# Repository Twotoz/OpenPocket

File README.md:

<p align="center">

</p>

<p align="center">
  <strong>A compact all-in-one ESP32-S3 handheld PCB combining RivetTX, ExpressLRS, RX5808 video, AT7456E OSD, and an AMT630A-driven 5-inch TFT.</strong>
</p>

<p align="center"><em>Revision-A top and bottom placement previews — production-board text and signal routing intentionally omitted.</em></p>

<p align="center">
  <a href="#why-openpocket">Why OpenPocket</a> ·
  <a href="#architecture">Architecture</a> ·
  <a href="#hardware">Hardware</a> ·
  <a href="#build-path">Build path</a> ·
  <a href="#firmware">Firmware</a> ·
  <a href="#documentation">Documentation</a>
</p>

> [!CAUTION]
> OpenPocket is an engineering prototype, not a flight-proven product. Build
> the first revision on a current-limited bench supply. Keep propellers removed
> and mechanisms safe until your exact transmitter, failsafe, power system,
> RF link, and video chain have passed hardware-in-the-loop validation.

## Why OpenPocket

OpenPocket puts the controls, live analog FPV picture, and transmitter menus in
one compact handheld. It uses the existing RivetTX OpenPocket character
compositor unchanged and connects it to a physical AT7456E video-overlay
backend. The ESP32 never has to capture or process video pixels.

| | |
|---|---|
| **One handheld** | Gimbals, switches, ExpressLRS control, telemetry, video, and menus in a single enclosure. |
| **Purpose-built MCU** | ESP32-S3 provides the GPIO, native USB, and task separation needed by the complete controller. |
| **Low-latency video** | RX5808 composite video passes through the AT7456E into an AMT630A TFT controller without digital capture. |
| **Integrated snow-screen display** | The PCB-installed AMT630A keeps weak or lost analog video visible as noise instead of hiding it behind a blue screen. |
| **Native analog OSD** | PAL/NTSC autodetection, a 30×16 character grid, custom glyphs, delta updates, and video-loss recovery. |
| **Bounded background work** | OSD and receiver services cannot delay control, CRSF, or telemetry processing. |
| **Open development path** | Wiring, BOM decisions, bring-up evidence, and future KiCad sources live in this repository. |

## Architecture

The flight-control path stays short while video and presentation work run as
bounded services.

```mermaid
flowchart LR
    A[Gimbals + switches] --> B[ESP32-S3<br/>RivetTX]
    B --> C[CRSF UART]
    C --> D[ExpressLRS<br/>TX module]

    E[5.8 GHz antenna] --> F[RX5808]
    F -->|composite video| G[AT7456E]
    G -->|internal PCB trace| H[AMT630A<br/>on the same PCB]
    H -->|24-bit RGB + sync| I[AT050TN33 V.1<br/>40-pin TFT]

    B -->|tune + RSSI| F
    B -->|bounded SPI| G
    D -->|telemetry| B

    classDef control fill:#102a43,stroke:#38bdf8,color:#f8fafc;
    classDef video fill:#26163f,stroke:#a78bfa,color:#f5f3ff;
    class A,B,C,D control;
    class E,F,G,H,I video;
```

The 250 Hz control task owns channel output and safety. The OSD driver advances
a non-blocking state machine and writes only changed character runs. Video
loss, PAL/NTSC changes, or an absent OSD chip must never hold up the control
path.

## Hardware

| Component | Role |
|---|---|
| ESP32-S3-MINI-1U-N8 | PCB-installed RivetTX MCU, native USB, 8 MiB flash, no PSRAM |
| user-installed ExpressLRS nano receiver | four-wire full-duplex CRSF control and telemetry link |
| PCBWay-installed RX5808 module | tunable 5.8 GHz analog receiver, internal composite video, and RSSI |
| PCB-installed AT7456E | PAL/NTSC character overlay in the internal video path |
| PCB-installed AMT630A and flash | PAL/NTSC composite decoding and direct 24-bit RGB panel drive |
| AT050TN33 V.1-compatible TFT | user-plugged 40-pin panel; arbitrary 40-pin TFTs are unsupported |
| two dual-axis gimbals | four primary analog control axes |
| switches, menu buttons, and optional encoder | arming, AUX controls, navigation, and editing |
| validated regulators and protection | clean supplies sized for RF, display, video, and logic peaks |

The ESP32-S3 is the OpenPocket target. RivetTX may support smaller ESP32-C3
transmitters, but the C3 is not the reference platform for this handheld. See
[ADR-0001](docs/decisions/0001-esp32-s3.md) for the decision record.

## Analog OSD

The existing RivetTX compositor produces a hardware-independent 30-column by
16-row character frame. The AT7456E backend then provides:

- PAL/NTSC autodetection and safe standard changes without a reboot
- all 30×16 cells in PAL, with essential content held inside 30×13 for NTSC
- custom character uploads for icons, selection markers, and warnings
- shadow-frame comparison so unchanged cells generate no SPI traffic
- bounded asynchronous transfers instead of full-screen blocking redraws
- communication retry/backoff and redraw after video loss or recovery

The RX5808 feeds baseband video to the AT7456E over an internal PCB trace; the
AT7456E overlays text and passes it internally to the AMT630A, which drives the
edge-connected TFT directly. The user never wires composite video. The
AMT630A's internal OSD is not used for OpenPocket menus. See the
[complete wiring guide](docs/wiring.md).

## Build path

Bring up one subsystem at a time:

1. Review the [Revision-A engineering package](hardware/rev-a/README.md) and
   resolve every machine-readable release blocker.
2. Complete independent schematic, layout, sourcing, and Gerber reviews.
3. Assemble first articles through PCBWay with the RX5808 consigned/manual
   operation and no unapproved substitutions.
4. Power the board from a current-limited source and validate rails before
   inserting the TFT, battery, or ExpressLRS receiver.
5. Complete the factory and HIL gates before any propeller-on use.

The [bench build guide](docs/build-guide.md) contains the full sequence and
stop conditions. Do not order from provisional files or bypass the release
gate in `hardware/rev-a`.

## Firmware

OpenPocket runs the `main` branch of
[Twotoz/RivetTX](https://github.com/Twotoz/RivetTX):

```bash
git clone https://github.com/Twotoz/RivetTX.git
cd RivetTX
idf.py set-target esp32s3
idf.py menuconfig
idf.py build
idf.py flash monitor
```

Use RivetTX's checked-in `sdkconfig.openpocket-rev-a.defaults`; it contains the
authoritative no-PSRAM, 8 MiB flash configuration and GPIO map matching this
board. See the [firmware guide](docs/firmware.md) for the complete configuration.

## Documentation

| Document | Contents |
|---|---|
| [Bill of materials](docs/bom.md) | prototype parts, electrical requirements, and unresolved selections |
| [Wiring](docs/wiring.md) | ESP32-S3, RX5808, AT7456E, AMT630A, TFT, and ExpressLRS interconnects |
| [Bench build guide](docs/build-guide.md) | staged assembly sequence and stop conditions |
| [Firmware](docs/firmware.md) | ESP32-S3 target setup and RivetTX OSD configuration |
| [Bring-up checklist](docs/bring-up.md) | electrical, control, PAL/NTSC, failure-recovery, and endurance tests |
| [Architecture](docs/architecture.md) | task boundaries, character presentation, and video path |
| [ESP32-S3 decision](docs/decisions/0001-esp32-s3.md) | why OpenPocket standardizes on the S3 |
| [AMT630A display decision](docs/decisions/0002-amt630a-snow-screen.md) | why the display stage uses a snow-screen AMT630A board |
| [Hardware sources](hardware/README.md) | scope and release policy for future KiCad and production files |
| [Revision-A package](hardware/rev-a/README.md) | integrated board constraints, GPIO, power, BOM, factory test, and release gates |
| [AMT630A firmware](display/amt630a/README.md) | target behavior, provenance requirements, and deterministic build gate |

## Project status

RivetTX contains the character OSD and physical RX5808/AT7456E services, with
host coverage for PAL, NTSC, UI, tuning, scanning, RSSI, delta updates, glyphs,
loss/recovery, and failure isolation. Revision-A startup ordering, board power
policy, and the no-PSRAM pin/partition profile are under review.

No PCB order package is released yet. The exact panel datasheet, AMT630A
firmware rights/provenance, selected RX5808 consigned module, sourcing review,
KiCad ERC/DRC, Gerber inspection, and physical HIL evidence remain open. This
is intentionally an engineering prototype, not a production-ready product.

## Contributing

Issues, schematic reviews, module measurements, and focused pull requests are
welcome. Hardware findings must identify the exact module revision, voltage,
firmware commit, measurement point, and PAL/NTSC source. See
[CONTRIBUTING.md](CONTRIBUTING.md).

## License

OpenPocket documentation and future hardware sources are released under the
[MIT License](LICENSE). RivetTX is maintained in its own repository under its
own license.

---

<p align="center">
  <sub>Built for open hardware experimentation, low-latency analog FPV, and careful validation.</sub>
</p>

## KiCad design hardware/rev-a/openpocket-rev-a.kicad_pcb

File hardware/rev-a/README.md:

# OpenPocket Revision A — Engineering Prototype

Revision A is a 115 mm × 72 mm, eight-layer, all-in-one transmitter board based
on the ESP32-S3-MINI-1U-N8. The intended assembled signal path is:

```text
5.8 GHz antenna -> RX5808 -> AT7456E -> AMT630A -> 40-pin ER-TFT050A3-2
```

Composite video never leaves the PCB. JLCPCB Standard PCBA is the primary
assembly target, with pre-order and consigned-RX5808 variants; the design is
vendor-neutral. The user installs
only the TFT panel, controls, one wired protected 1S battery connection,
antennas, a pre-flashed ExpressLRS nano receiver, and the enclosure.

## Release state

This directory is an engineering-review package, not an order package. The
release script intentionally refuses to generate Gerbers or a manufacturing
ZIP until every blocking item in `release-status.json` is resolved with a
reviewed source artifact.

The generated KiCad draft has a clean ERC and a completed L2 ground fanout,
but signal routing and final DRC remain incomplete. It is therefore not a
fabrication/order package. The source-built AMT630A firmware and circuit
research may be reviewed independently, but they do not waive schematic,
layout, Gerber and first-article gates. Software tests are not hardware
validation.

## Design constraints

- 115 mm × 72 mm fixed outline.
- Eight layers, 1.0 mm finished thickness, 1 oz copper, ENIG.
- L1/L8 components and critical routing, uninterrupted L2/L7 ground, and six
  available routing layers for signals and width-controlled power routes.
- RX5808 on the bottom side with shield, solder-joint, antenna and inspection
  clearances; J11 U.FL/MHF1 is also bottom-side for a via-free 5.8 GHz feed.
- AMT630A next to the edge-mounted TFT connector; AT7456E on the short analog
  path between RX5808 and AMT630A.
- Backlight switching and power converters stay outside the analog/RF region.
- Separate ESP32, ELRS 2.4 GHz, and RX5808 5.8 GHz antenna regions.
- Dedicated user-accessible push-push microSD at 1-bit/20 MHz maximum, with
  switched power and enclosure finger/eject clearance.
- Board marking: `OpenPocket Rev A` and `Engineering Prototype`.

## Contents

| File | Purpose |
|---|---|
| `gpio-map.md` | authoritative ESP32 and expander allocation |
| `microsd.md` | SDMMC circuit, socket audit, limits and acceptance tests |
| `wiring.md` | internal and user-installed connections |
| `power-budget.md` | preliminary worst-case and thermal calculations |
| `routing-constraints.md` | KiCad netclasses, widths, vias and routing order |
| `stackup.md` | nominal 1.0 mm eight-layer construction and impedance sign-off gate |
| `bom.csv` | controlled component selection and verification state |
| `dnp.csv` | optional/DNP items |
| `consigned-parts.csv` | RX5808 manual-assembly requirement |
| `release-status.json` | machine-readable evidence and blockers |
| `factory-test.md` | pass/fail protocol and first-article sequence |
| `pcbway-notes.md` | stack-up, assembly, inspection, and substitution rules |
| `tools/release_gate.py` | refuses an unsafe manufacturing release |

Fabrication outputs and a versioned release ZIP must only be generated after
the KiCad sources pass review, ERC, DRC and independent Gerber inspection.

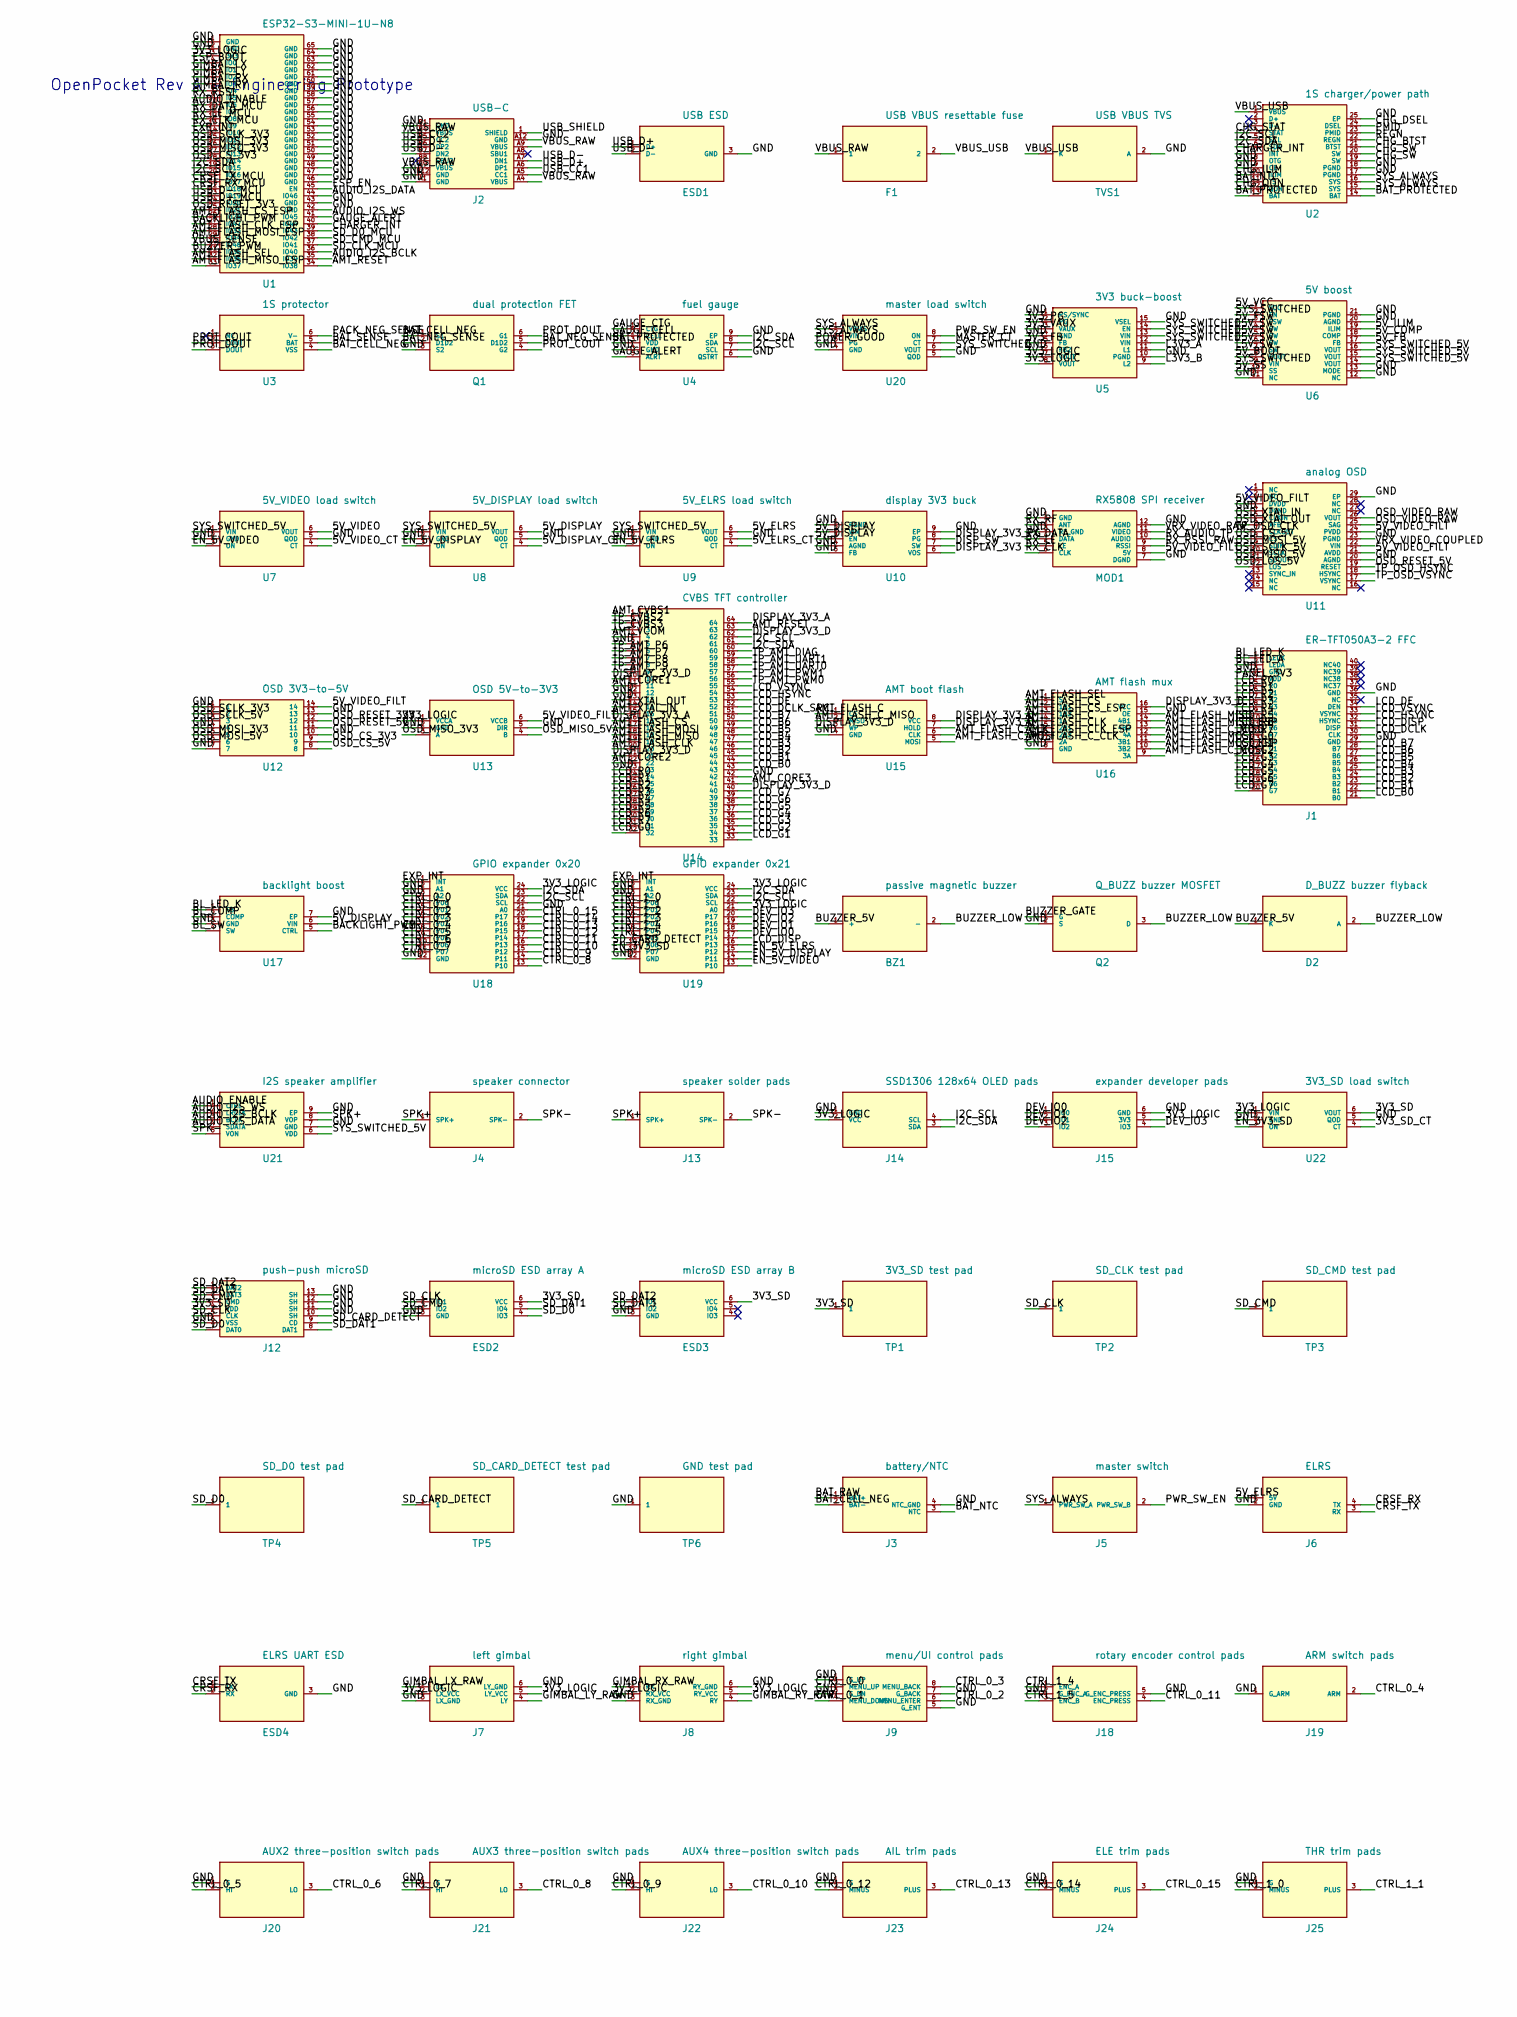
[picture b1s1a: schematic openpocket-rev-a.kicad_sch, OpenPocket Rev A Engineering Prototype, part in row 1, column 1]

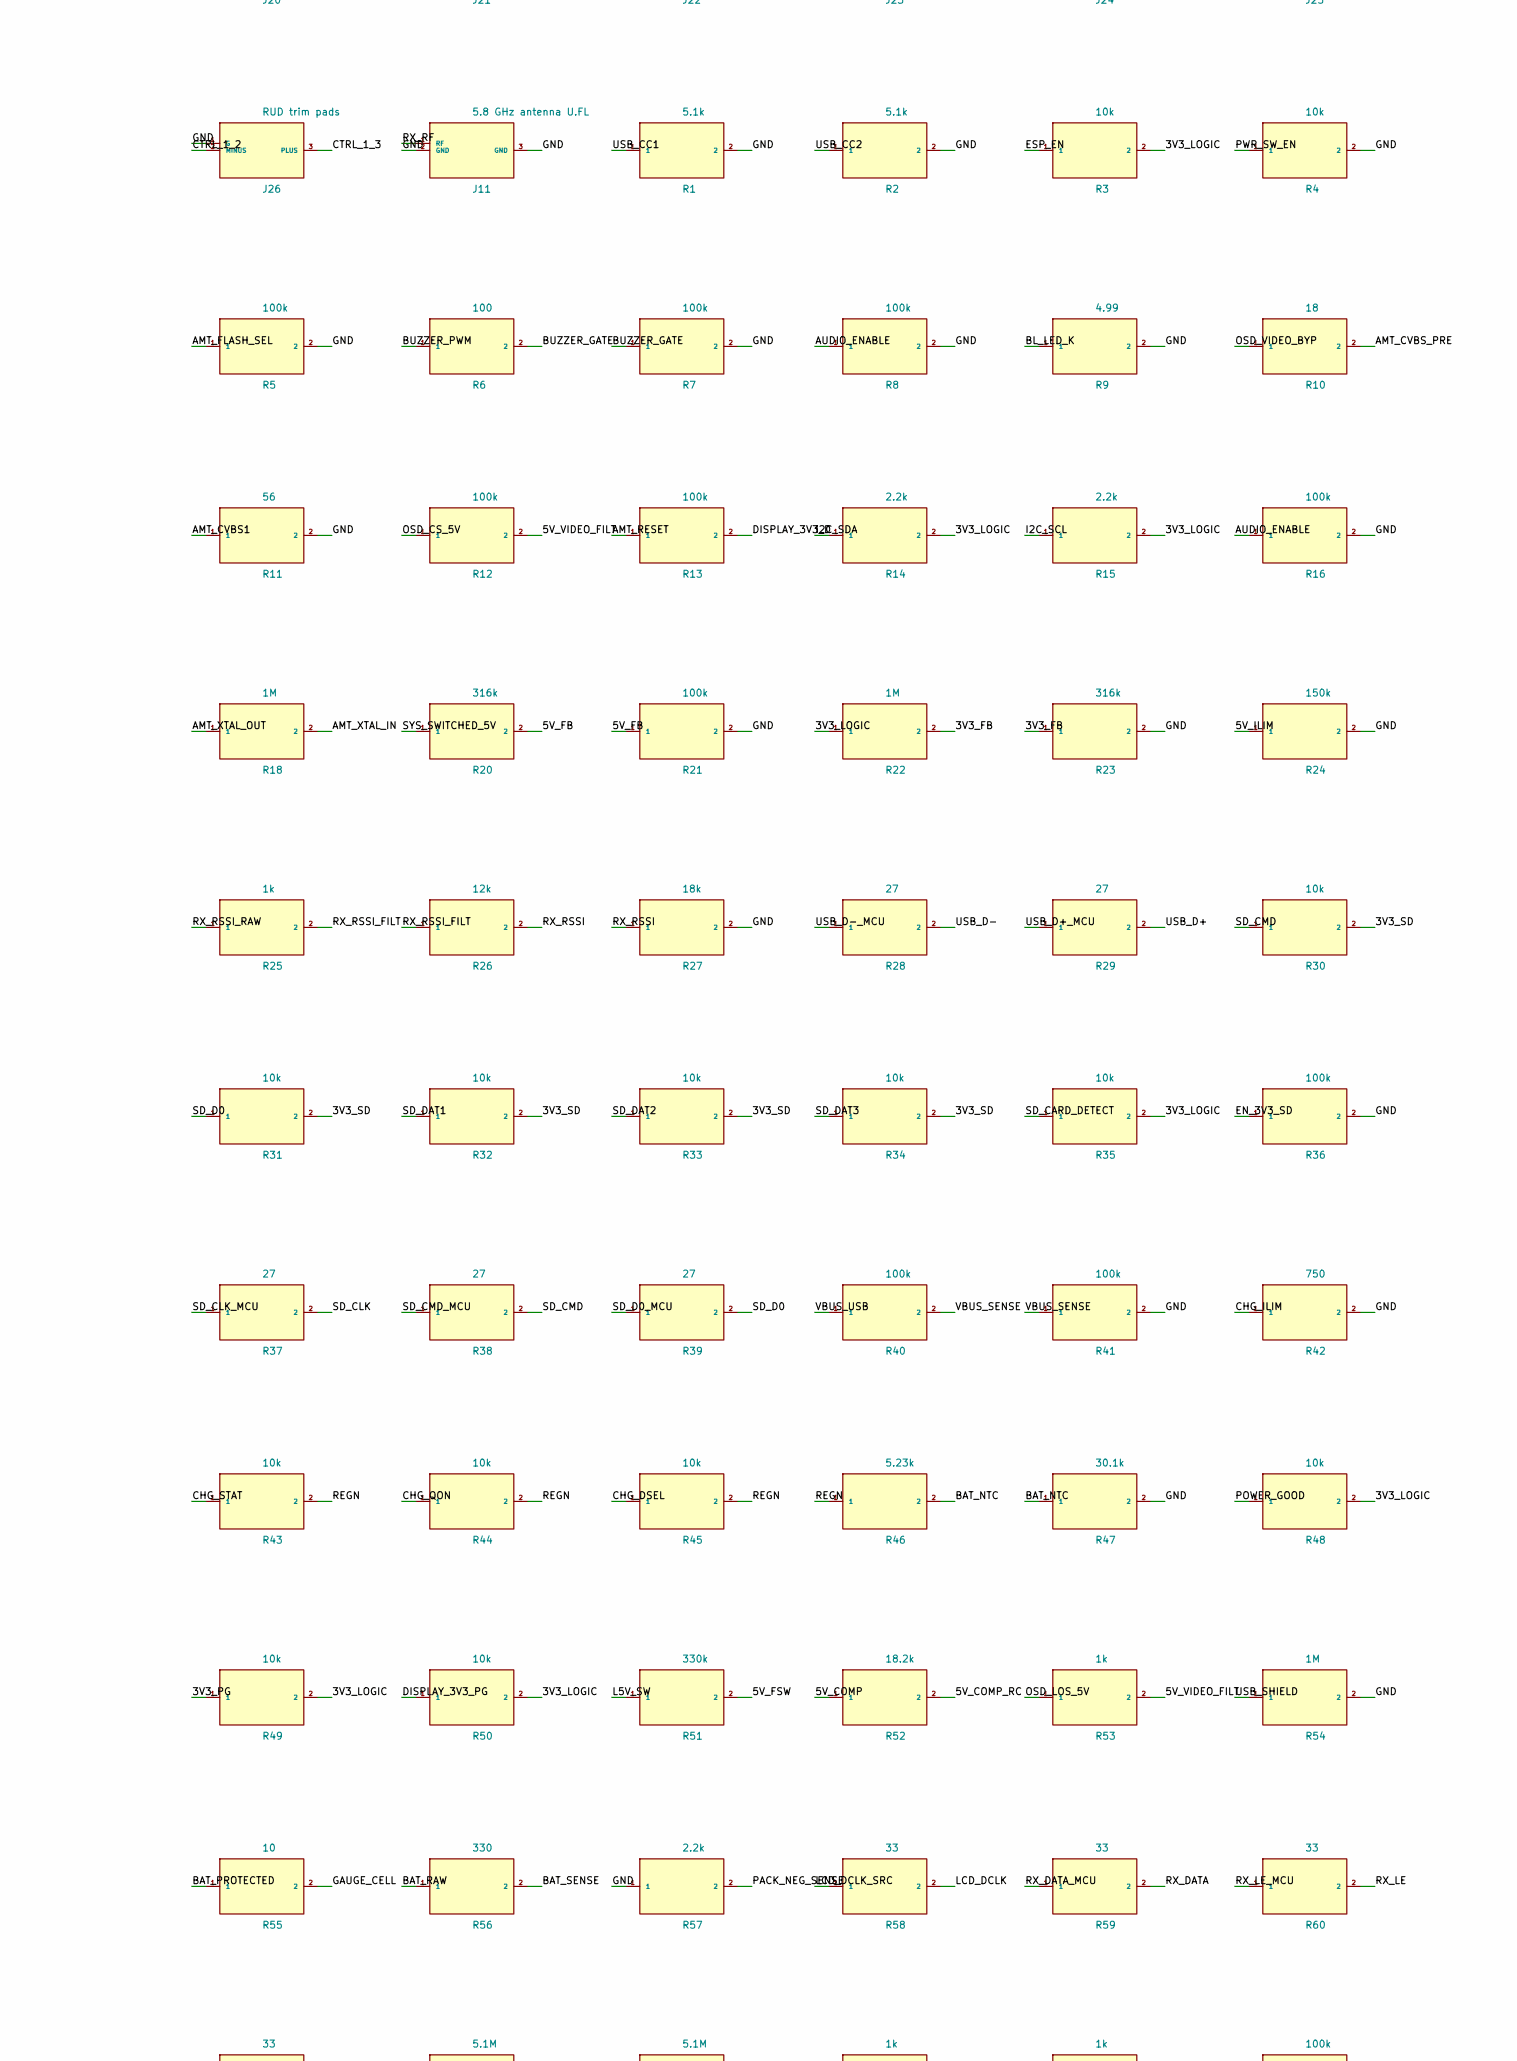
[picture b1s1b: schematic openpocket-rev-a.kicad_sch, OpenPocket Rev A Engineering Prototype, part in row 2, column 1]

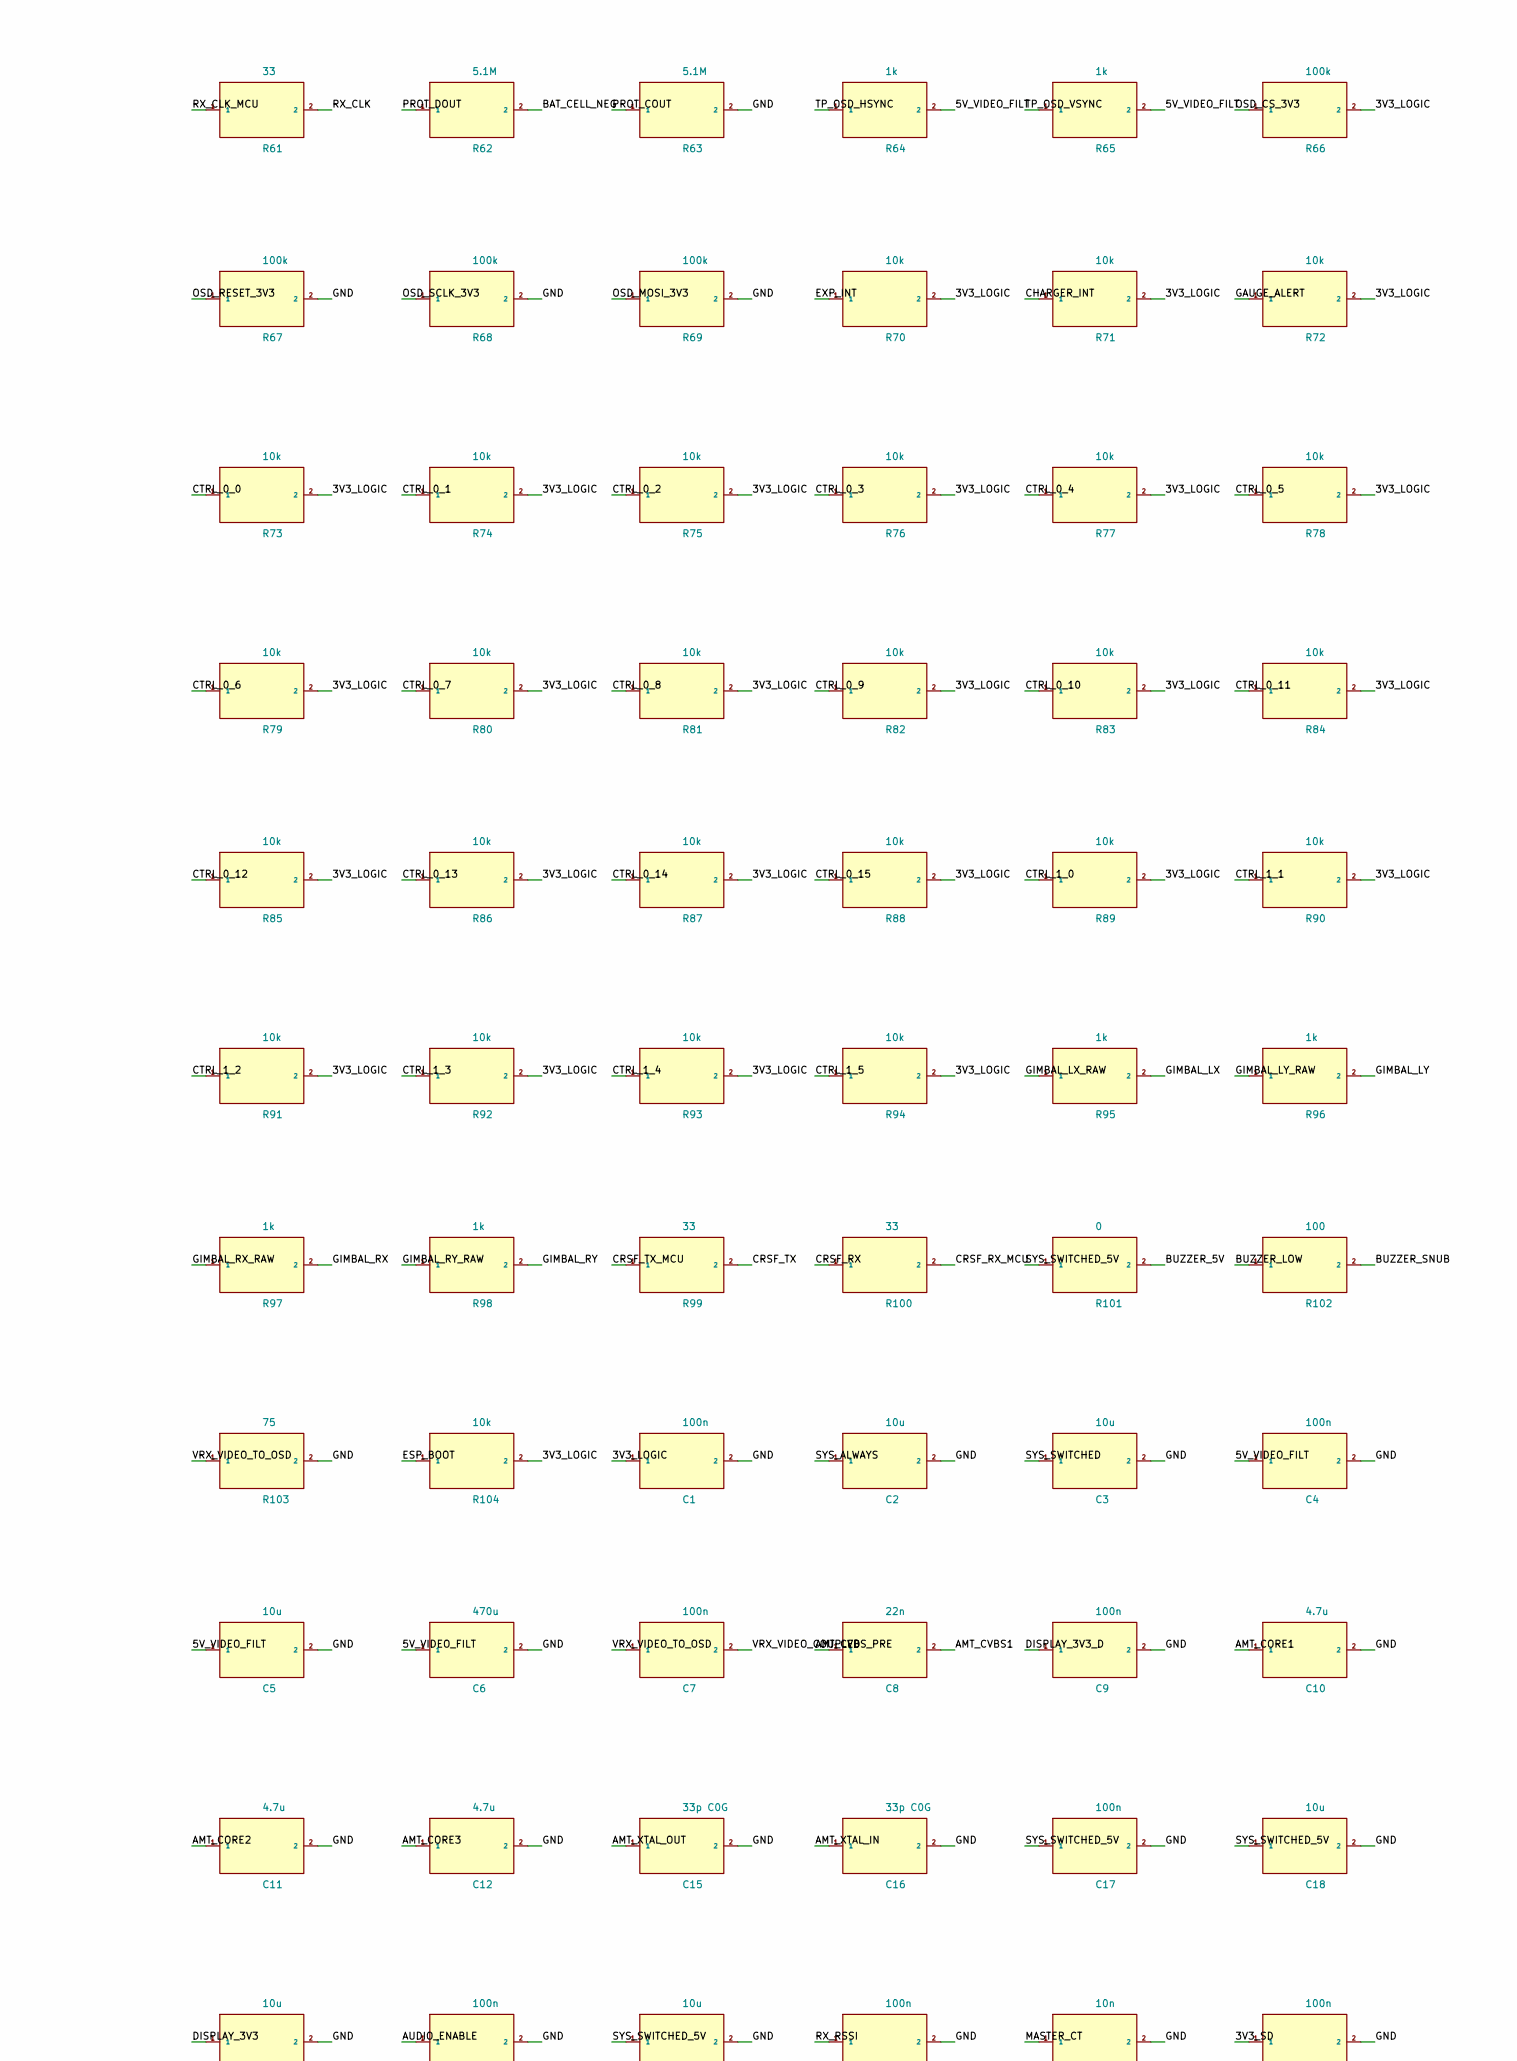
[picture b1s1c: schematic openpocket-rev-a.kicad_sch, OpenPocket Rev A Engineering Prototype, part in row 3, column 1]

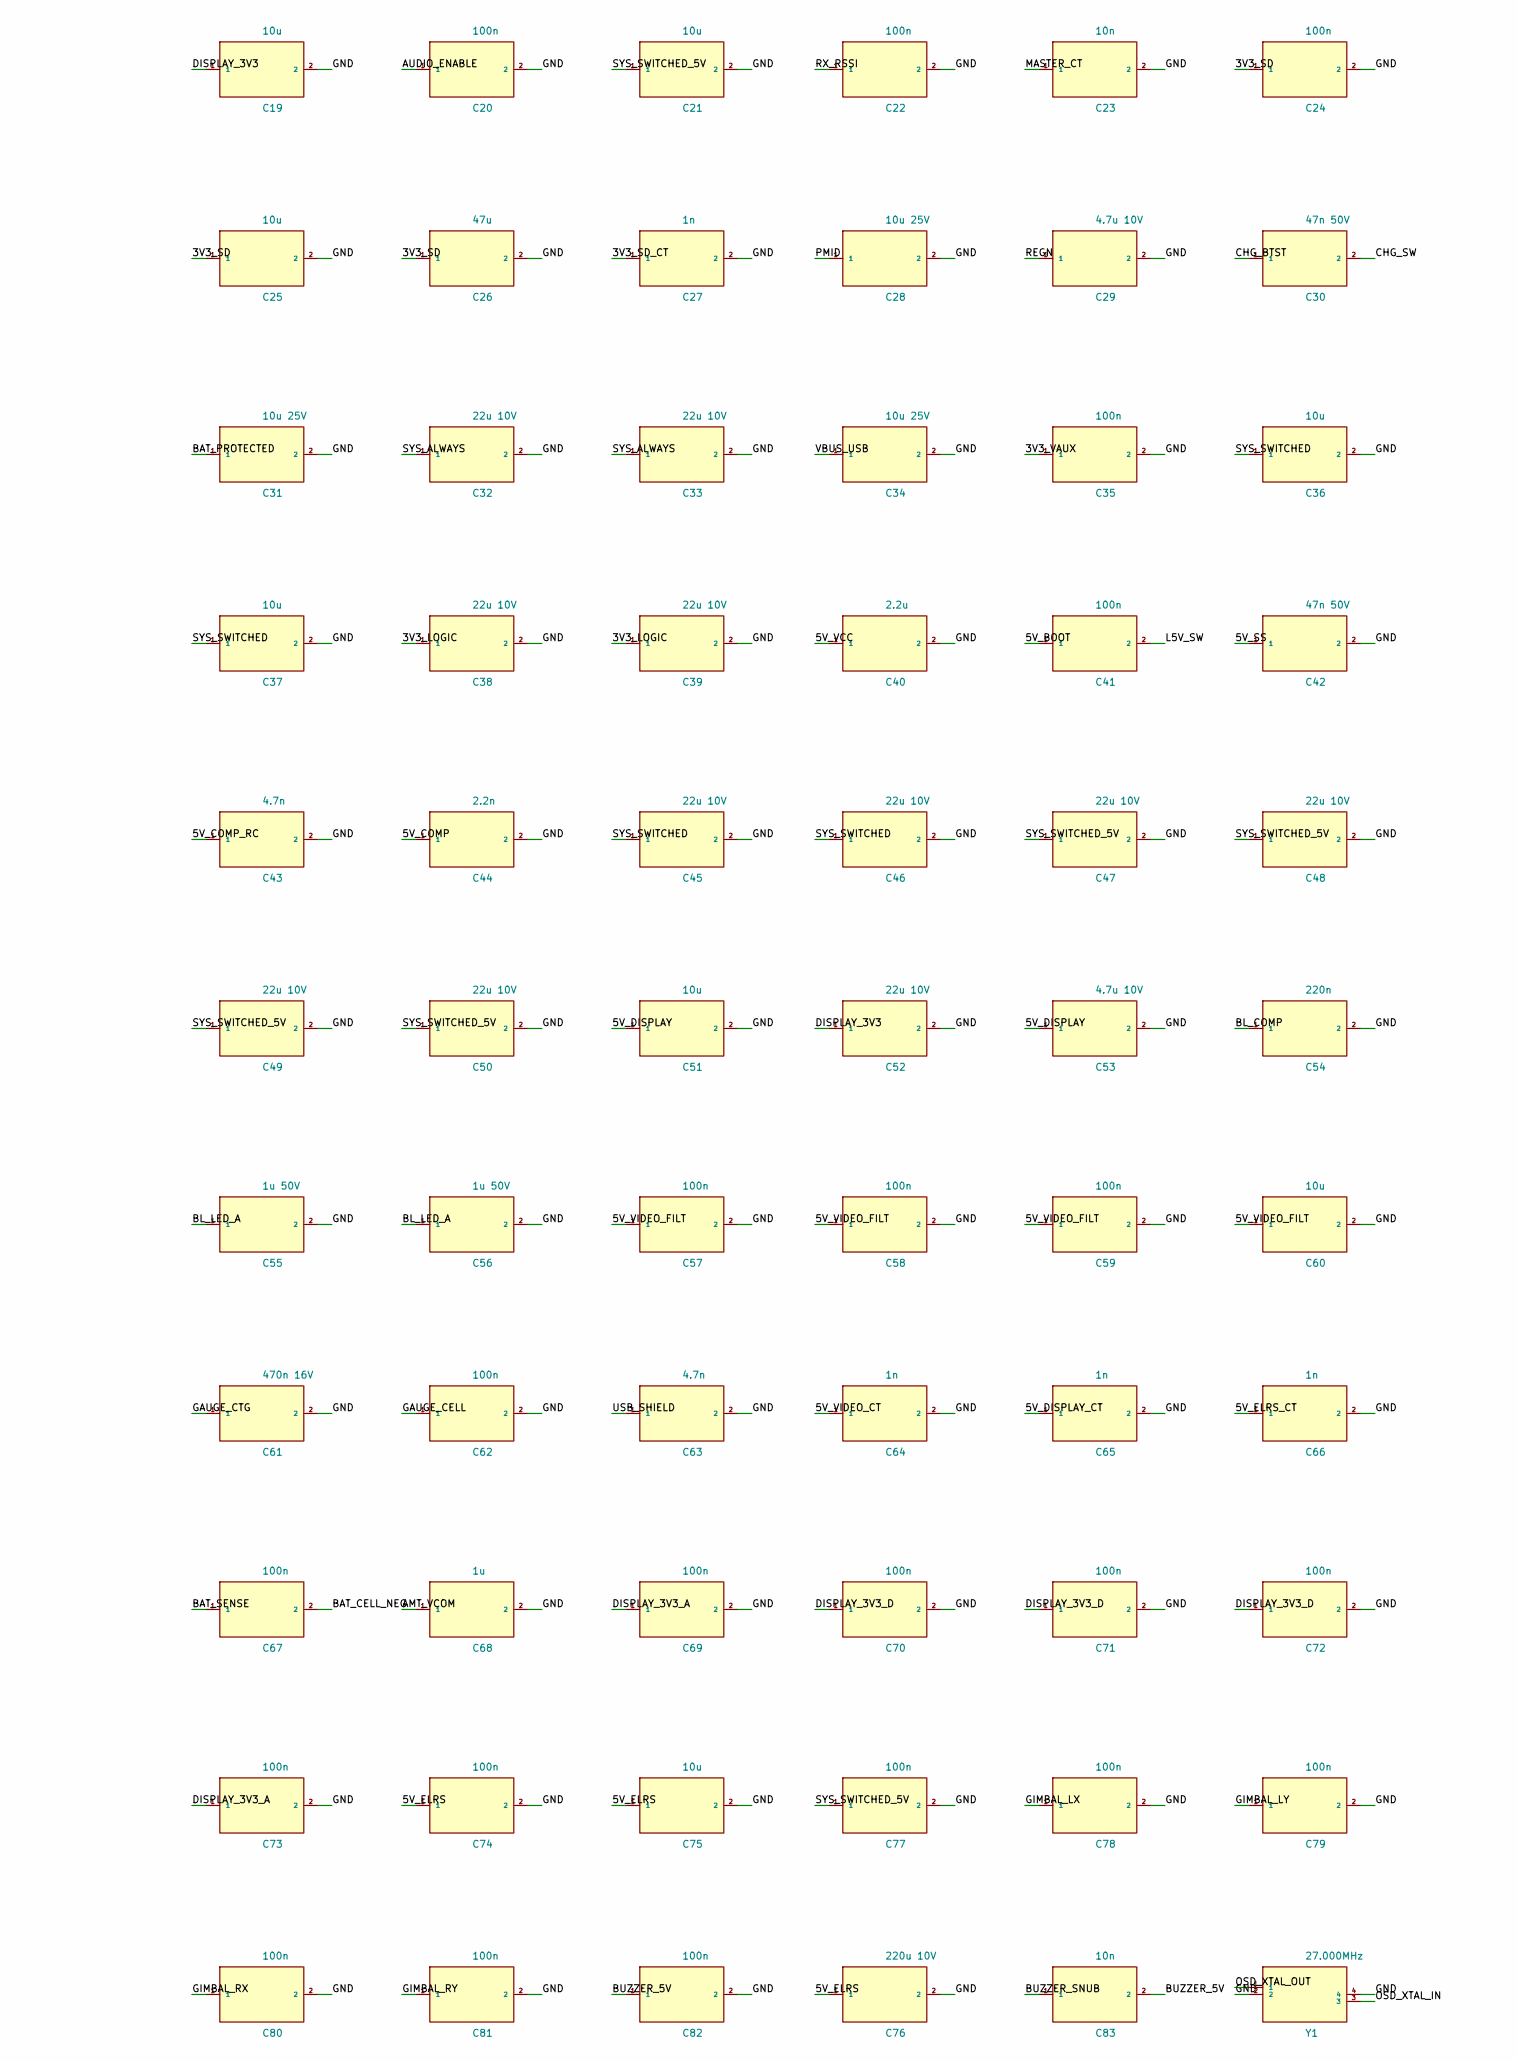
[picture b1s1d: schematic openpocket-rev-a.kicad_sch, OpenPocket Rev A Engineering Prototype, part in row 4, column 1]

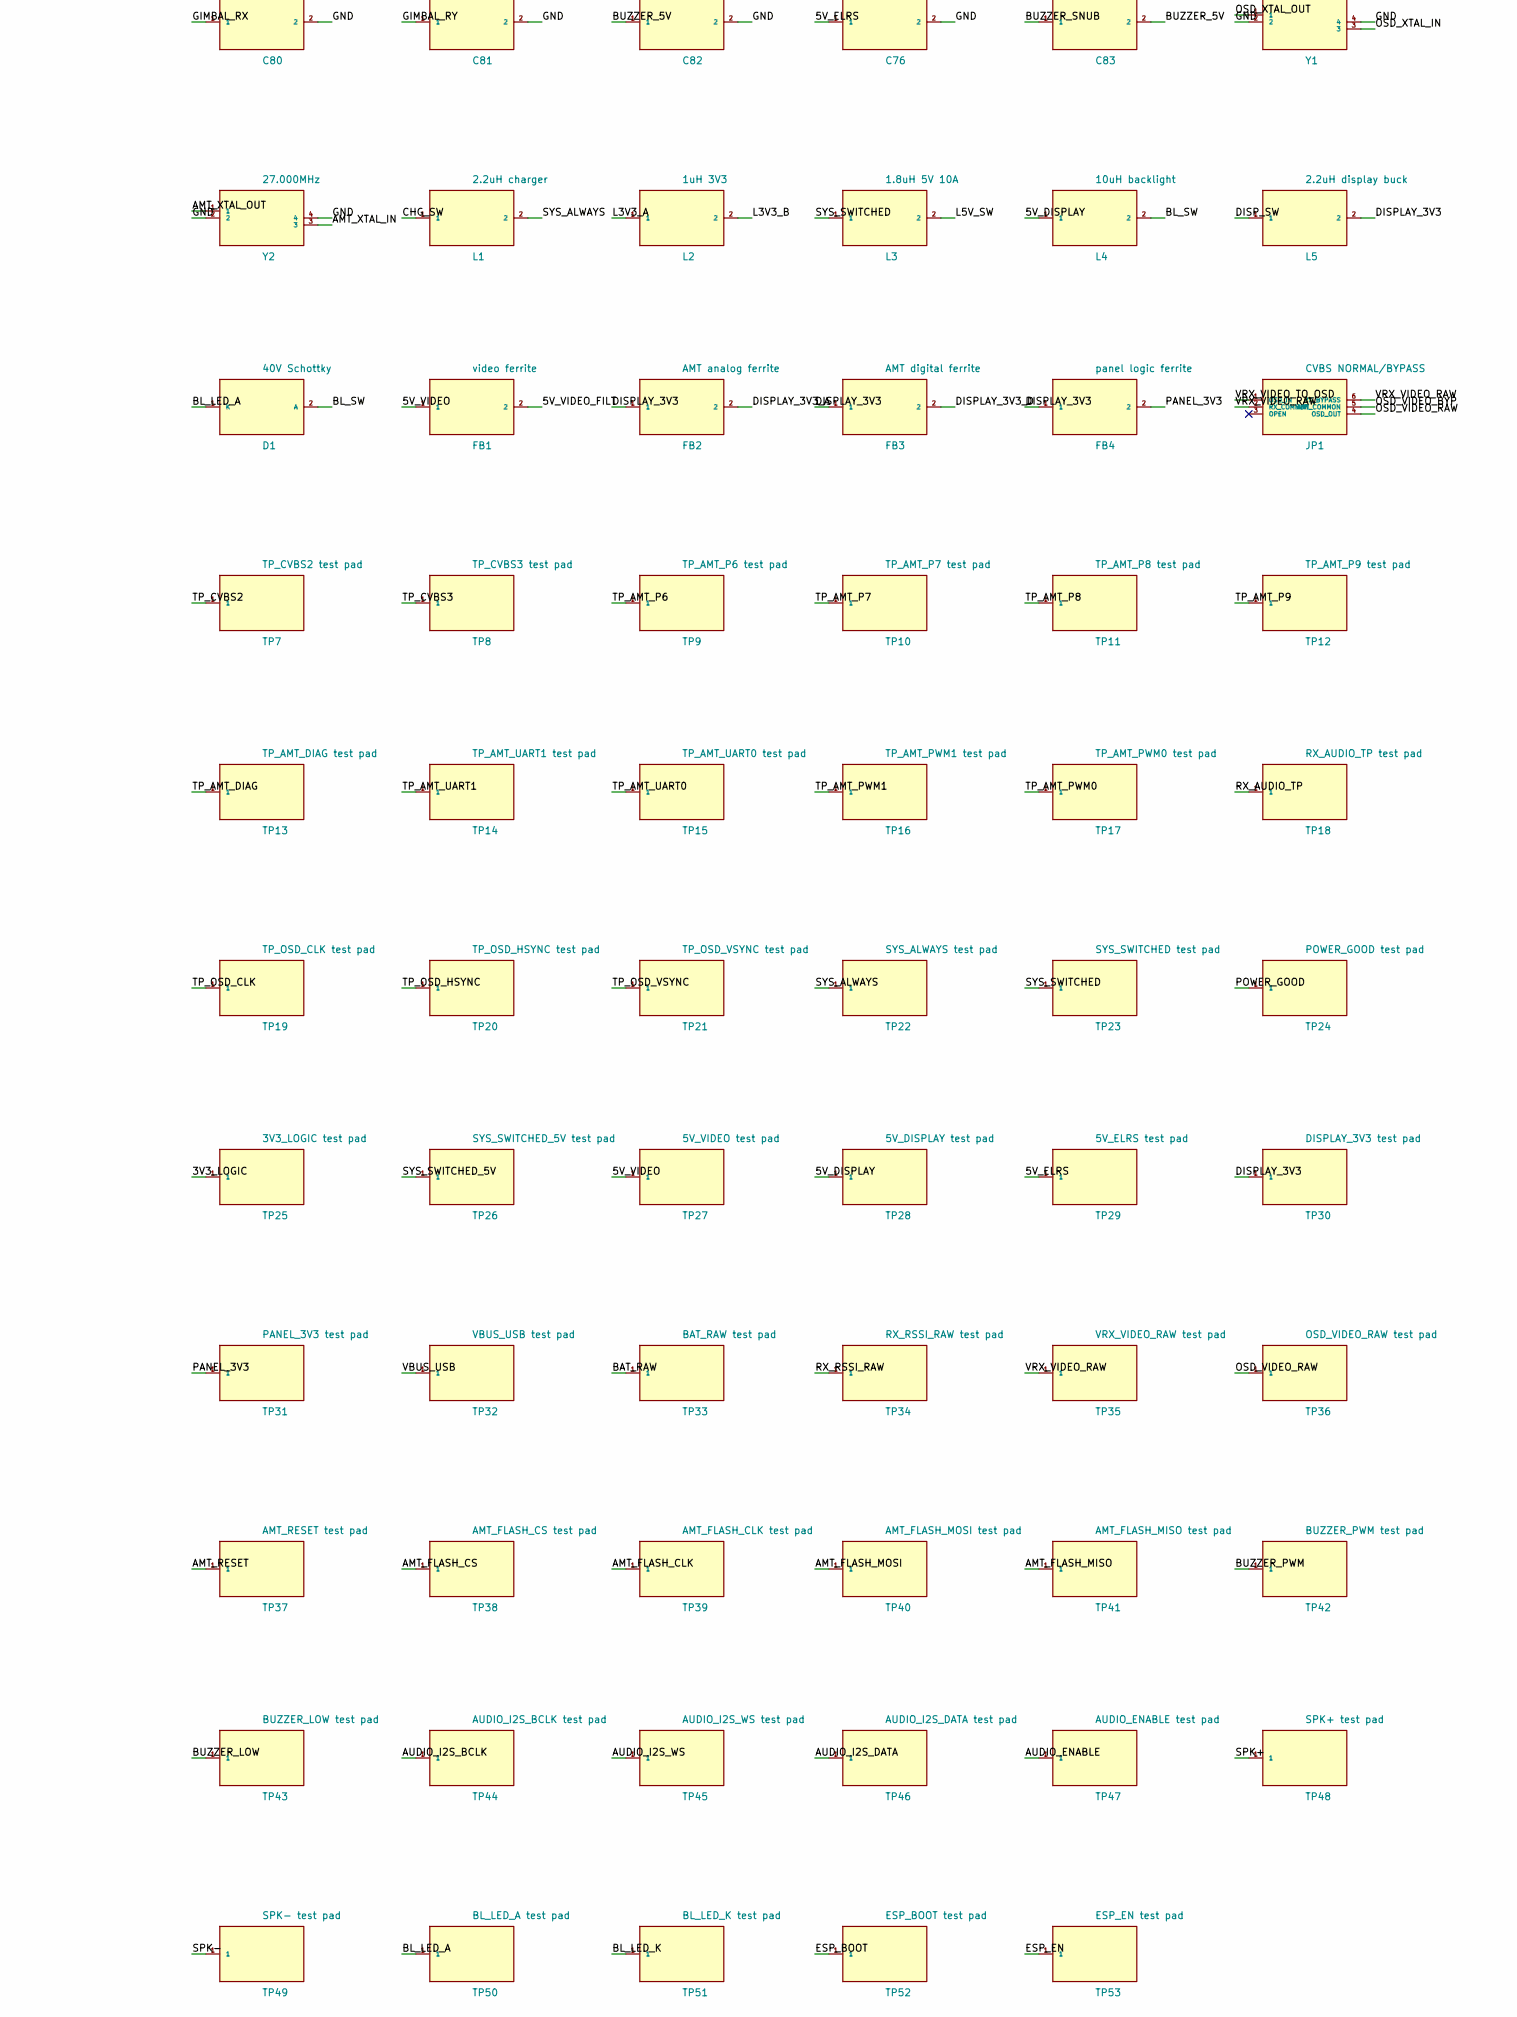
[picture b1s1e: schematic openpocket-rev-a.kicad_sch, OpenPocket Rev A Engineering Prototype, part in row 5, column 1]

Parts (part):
BZ1: passive magnetic buzzer; SMD-7.5x7.5; MPN YS-SBZ7525C05R30; LCSC C7421675
C1, C4, C7, C9, C17, C20, C22, C24, C35, C41, C57, C58, C59, C62, C67, C69, C70, C71, C72, C73, C74, C77, C78, C79, C80, C81, C82: 100n; C0402; MPN CL05B104KO5NNNC; LCSC C1525
C2, C3, C5, C18, C19, C21, C25, C36, C37, C51, C60, C75: 10u; C0805; MPN CL21A106KAYNNNE; LCSC C15850
C6: 470u; SMD-D10; MPN VZH471M1ATR-1008; LCSC C249929
C8: 22n; C0402; MPN CL05B223KB5NNNC; LCSC C337699
C10, C11, C12: 4.7u; C0603; MPN CL10A475KP8NNNC; LCSC C1705
C15, C16: 33p C0G; C0402; MPN CC0402JRNPO9BN330; LCSC C107005
C23, C83: 10n; C0402; MPN CL05B103KB5NNNC; LCSC C15195
C26: 47u; C1206; MPN CL31A476MPHNNNE; LCSC C96123
C27, C64, C65, C66: 1n; C0402; MPN CL05B102KB5NNNC; LCSC C14442
C28, C31, C34: 10u 25V; C0805; MPN CGA0805X7R106K250MT; LCSC C6119932
C29, C53: 4.7u 10V; 0603; MPN 0603B475K100NT; LCSC C108342
C30, C42: 47n 50V; C0402; MPN CC0402KRX7R9BB473; LCSC C272875
C32, C33, C38, C39, C45, C46, C47, C48, C49, C50, C52: 22u 10V; C0805; MPN CGA0805X7R226M100MT; LCSC C23692981
C40: 2.2u; C0603; MPN CL10A225KO8NNNC; LCSC C23630
C43, C63: 4.7n; C0402; MPN CL05B472KB5NNNC; LCSC C84705
C44: 2.2n; C0402; MPN CL05B222KB5NNNC; LCSC C84703
C54: 220n; C0402; MPN CC0402KRX7R8BB224; LCSC C723566
C55, C56: 1u 50V; C0805; MPN CC0805KKX7R9BB105; LCSC C91185
C61: 470n 16V; 0402; MPN CGA0402X7R474K160GT; LCSC C22435970
C68: 1u; C0402; MPN CL05A105KA5NQNC; LCSC C52923
C76: 220u 10V; CAP-SMD_BD8.0-L8.3-W8.3-FD; MPN EEEFK1A221P; LCSC C401648
D1: 40V Schottky; SMA_L4.3-W2.6-LS5.2-RD; MPN B240A-13-F; LCSC C92506
D2: D_BUZZ buzzer flyback; SOD-123F_L2.7-W1.6-LS3.8-RD; MPN 1N4148W; LCSC C81598
ESD1: USB ESD; SOT-9X3-3_L1.0-W0.8-P0.35-LS1.0-BR; MPN TPD2EUSB30DRTR; LCSC C97502
ESD2: microSD ESD array A; SOT-563_L1.6-W1.2-P0.50-LS1.6-BL; MPN TPD4E001DRLR; LCSC C527516
ESD3: microSD ESD array B; SOT-563_L1.6-W1.2-P0.50-LS1.6-BL; MPN TPD4E001DRLR; LCSC C527516
ESD4: ELRS UART ESD; SOT-9X3-3_L1.0-W0.8-P0.35-LS1.0-BR; MPN TPD2EUSB30DRTR; LCSC C97502
F1: USB VBUS resettable fuse; F1206; MPN 1206L200PR; LCSC C151163
FB1: video ferrite; L0805; MPN BLM21PG221SN1D; LCSC C85840
FB2: AMT analog ferrite; L0603; MPN BLM18AG601SN1D; LCSC C19330
FB3: AMT digital ferrite; L0603; MPN BLM18AG601SN1D; LCSC C19330
FB4: panel logic ferrite; L0603; MPN BLM18AG601SN1D; LCSC C19330
J1: ER-TFT050A3-2 FFC; FPC-SMD_FH12-40S-0.5SH-55; MPN FH12-40S-0.5SH(55); LCSC C202114
J2: USB-C; TYPE-C-SMD_SBC-160S1A-20-S412; MPN USB4105-GF-A; LCSC C3020560
J3: battery/NTC; EDGE-PADS-4; MPN SOLDER-PADS-4; LCSC CONS
J4: speaker connector; CONN-SMD_P2.00_S2B-PH-SM4-TB-LF-SN; MPN S2B-PH-SM4-TB(LF)(SN); LCSC C295747
J5: master switch; EDGE-PADS-2; MPN SOLDER-PADS-2; LCSC CONS
J6: ELRS; EDGE-PADS-4; MPN SOLDER-PADS-4; LCSC CONS
J7: left gimbal; EDGE-PADS-6; MPN SOLDER-PADS-6; LCSC CONS
J8: right gimbal; EDGE-PADS-6; MPN SOLDER-PADS-6; LCSC CONS
J9: menu/UI control pads; MENU-CONTROL-PADS; MPN MENU-CONTROL-PADS; LCSC CONS
J11: 5.8 GHz antenna U.FL; U.FL; MPN U.FL-R-SMT-1(10); LCSC C88373
J12: push-push microSD; TF-001A-P3; MPN TF-001A-P3; LCSC C3021282
J13: speaker solder pads; EDGE-PADS-2; MPN SOLDER-PADS-2; LCSC CONS
J14: SSD1306 128x64 OLED pads; DEV-PADS-4; MPN DEV-PADS-4; LCSC CONS
J15: expander developer pads; DEV-PADS-6; MPN DEV-PADS-6; LCSC CONS
J18: rotary encoder control pads; ENCODER-CONTROL-PADS; MPN ENCODER-CONTROL-PADS; LCSC CONS
J19: ARM switch pads; ARM-CONTROL-PADS; MPN ARM-CONTROL-PADS; LCSC CONS
J20: AUX2 three-position switch pads; AUX2-CONTROL-PADS; MPN AUX2-CONTROL-PADS; LCSC CONS
J21: AUX3 three-position switch pads; AUX3-CONTROL-PADS; MPN AUX3-CONTROL-PADS; LCSC CONS
J22: AUX4 three-position switch pads; AUX4-CONTROL-PADS; MPN AUX4-CONTROL-PADS; LCSC CONS
J23: AIL trim pads; AIL-TRIM-PADS; MPN AIL-TRIM-PADS; LCSC CONS
J24: ELE trim pads; ELE-TRIM-PADS; MPN ELE-TRIM-PADS; LCSC CONS
J25: THR trim pads; THR-TRIM-PADS; MPN THR-TRIM-PADS; LCSC CONS
J26: RUD trim pads; RUD-TRIM-PADS; MPN RUD-TRIM-PADS; LCSC CONS
JP1: CVBS NORMAL/BYPASS; SOLDER-JUMPER-6; MPN SJ-DPDT; LCSC N/A
L1: 2.2uH charger; IND-SMD_L4.0-W4.0_LQH44PN2R2MP0L; MPN SWPA4030S2R2MT; LCSC C36409
L2: 1uH 3V3; IND-SMD_L4.0-W4.0_SWPA40XXS; MPN SWPA4020S1R0MT; LCSC C142484
L3: 1.8uH 5V 10A; IND-SMD_L6.6-W6.4-P4.04_XAL6030-182MEC; MPN XAL6030-182MEC; LCSC C19191693
L4: 10uH backlight; IND-SMD_L4.0-W4.0_SLW4010S; MPN SWPA4020S100MT; LCSC C82398
L5: 2.2uH display buck; IND-SMD_L3.0-W3.0; MPN SWPA3015S2R2MT; LCSC C43389
MOD1: RX5808 SPI receiver; COMM-SMD_12P_RX5808; MPN RX5808 SPI-modified; LCSC C2908157
Q1: dual protection FET; SOT-23-6_L2.9-W1.6-P0.95-LS2.8-BR; MPN FS8205A; LCSC C908265
Q2: Q_BUZZ buzzer MOSFET; SOT-23-3_L2.9-W1.3-P1.90-LS2.4-BR; MPN AO3400A; LCSC C20917
R1, R2: 5.1k; R0402; MPN RC0402FR-075K1L; LCSC C105872
R3, R4, R30, R31, R32, R33, R34, R35, R43, R44, R45, R48, R49, R50, R70, R71, R72, R73, R74, R75, R76, R77, R78, R79, R80, R81, R82, R83, R84, R85, R86, R87, R88, R89, R90, R91, R92, R93, R94, R104: 10k; R0402; MPN RC0402FR-0710KL; LCSC C60490
R5, R7, R8, R12, R13, R16, R21, R36, R40, R41, R66, R67, R68, R69: 100k; R0402; MPN RC0402FR-07100KL; LCSC C60491
R6, R102: 100; R0402; MPN RC0402FR-07100RL; LCSC C106232
R9: 4.99; R0603; MPN RC0603FR-074R99L; LCSC C137704
R10: 18; R0603; MPN RC0603FR-0718RL; LCSC C245924
R11: 56; R0603; MPN RC0603FR-0756RL; LCSC C126360
R14, R15: 2.2k; R0402; MPN RC0402FR-072K2L; LCSC C114762
R18, R22, R54: 1M; R0402; MPN RC0402FR-071ML; LCSC C138033
R20, R23: 316k; R0402; MPN RC0402FR-07316KL; LCSC C185427
R24: 150k; R0402; MPN RC0402FR-07150KL; LCSC C93947
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
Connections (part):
3V3_FB: R22.2, R23.1, U5.5 (FB)
3V3_LOGIC: C1.1, C38.1, C39.1, J7.2 (LX_VCC), J7.5 (LY_VCC), J8.2 (RX_VCC), J8.5 (RY_VCC), J14.2 (VCC), J15.5 (3V3), R3.2, R14.2, R15.2, R22.1, R35.2, R48.2, R49.2, R50.2, R66.2, R70.2, R71.2, R72.2, R73.2, R74.2, R75.2, R76.2, R77.2, R78.2, R79.2, R80.2, R81.2, R82.2, R83.2, R84.2, R85.2, R86.2, R87.2, R88.2, R89.2, R90.2, R91.2, R92.2, R93.2, R94.2, R104.2, TP25.1, U1.3 (3V3), U5.7 (VOUT), U5.8 (VOUT), U13.1 (VCCA), U18.24 (VCC), U19.21 (A0), U19.24 (VCC), U22.1 (VIN)
3V3_PG: R49.1, U5.2 (PG)
3V3_SD: C24.1, C25.1, C26.1, ESD2.6 (VCC), ESD3.6 (VCC), J12.4 (VDD), R30.2, R31.2, R32.2, R33.2, R34.2, TP1.1, U22.6 (VOUT)
3V3_SD_CT: C27.1, U22.4 (CT)
3V3_VAUX: C35.1, U5.3 (VAUX)
5V_BOOT: C41.1, U6.8 (BOOT)
5V_COMP: C44.1, R52.1, U6.18 (COMP)
5V_COMP_RC: C43.1, R52.2
5V_DISPLAY: C51.1, C53.1, L4.1, TP28.1, U8.6 (VOUT), U10.2 (VIN), U10.3 (EN), U17.6 (VIN)
5V_DISPLAY_CT: C65.1, U8.4 (CT)
5V_ELRS: C74.1, C75.1, C76.1, J6.1 (5V), TP29.1, U9.6 (VOUT)
5V_ELRS_CT: C66.1, U9.4 (CT)
5V_FB: R20.2, R21.1, U6.17 (FB)
5V_FSW: R51.2, U6.3 (FSW)
5V_ILIM: R24.1, U6.19 (ILIM)
5V_SS: C42.1, U6.10 (SS)
5V_VCC: C40.1, U6.1 (VCC)
5V_VIDEO: FB1.1, TP27.1, U7.6 (VOUT)
5V_VIDEO_CT: C64.1, U7.4 (CT)
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
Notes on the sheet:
OpenPocket Rev A — Engineering Prototype

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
